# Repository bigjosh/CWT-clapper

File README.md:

# CWT-CLAPPER firmware, 2021 josh.com

## The mission

Be able to synchonise the clapping of the clappers, which requires sensing when the local clapper last clapped so that it can be positioned for the next clap. This is complicated becuase the only intentional sensor on board is a microphone and it is hard to differentiate beween the sound of a local clap and a nearby clap. 

## Theory of operation 

 1. As the cam rotates and pushes the blade, the spring is progessively streched. 
 2. The farther the spring is streched, the harder it is to strech it further (googgle "Hooke's law"). 
 3. The more force it takes to turn the motor, the more current it uses. 
 4. The more current the motor uses, the lower the voltage across the batteries becomes (google "internal resistance"). 
 5. We can indirectly measure the voltage across the battery with the internal ADC (https://wp.josh.com/2014/11/06/battery-fuel-guage-with-zero-parts-and-zero-pins-on-avr/)
 
 Q.E.D.: We can (sort of, barely, sextuple indirectly) measure the position of the blade by measuring the internal voltage 
 bandgap of the chip using the ADC!
  
 In practice, the change in ADC readings between the blade being fully open and fully shut is very small 
 and there is lots of noise also in these readings.
 
 So we aim to detect the most abupt change in that signal - the moment when the blade claps and the motor goes from pushing 
 a fully streched to spring to not pushing on the blade at all (there is a bit of a dead zone after a clap before the cam
 touches the blade again).
  
 To find this edge, we both filter out high freqnecy noise and amplify the longer running signal by taking periodic ADC samples 
 and summing these over a longer window. We have two consecutive windows, so when we get to the moment where one window is
 filled with samples from before the flap and the other is filled with samples from after the clap, there should be enough SNR to detect
 that by comparing the sums of all the values in each window. 
 
## Demo 
 
See them clap hare....
https://www.youtube.com/watch?v=MOf7x3NkilU&lc=UgzuyXRK9PwrqrHehkx4AaABAg.9SaJbr_eWT19Sc9pGRepJp

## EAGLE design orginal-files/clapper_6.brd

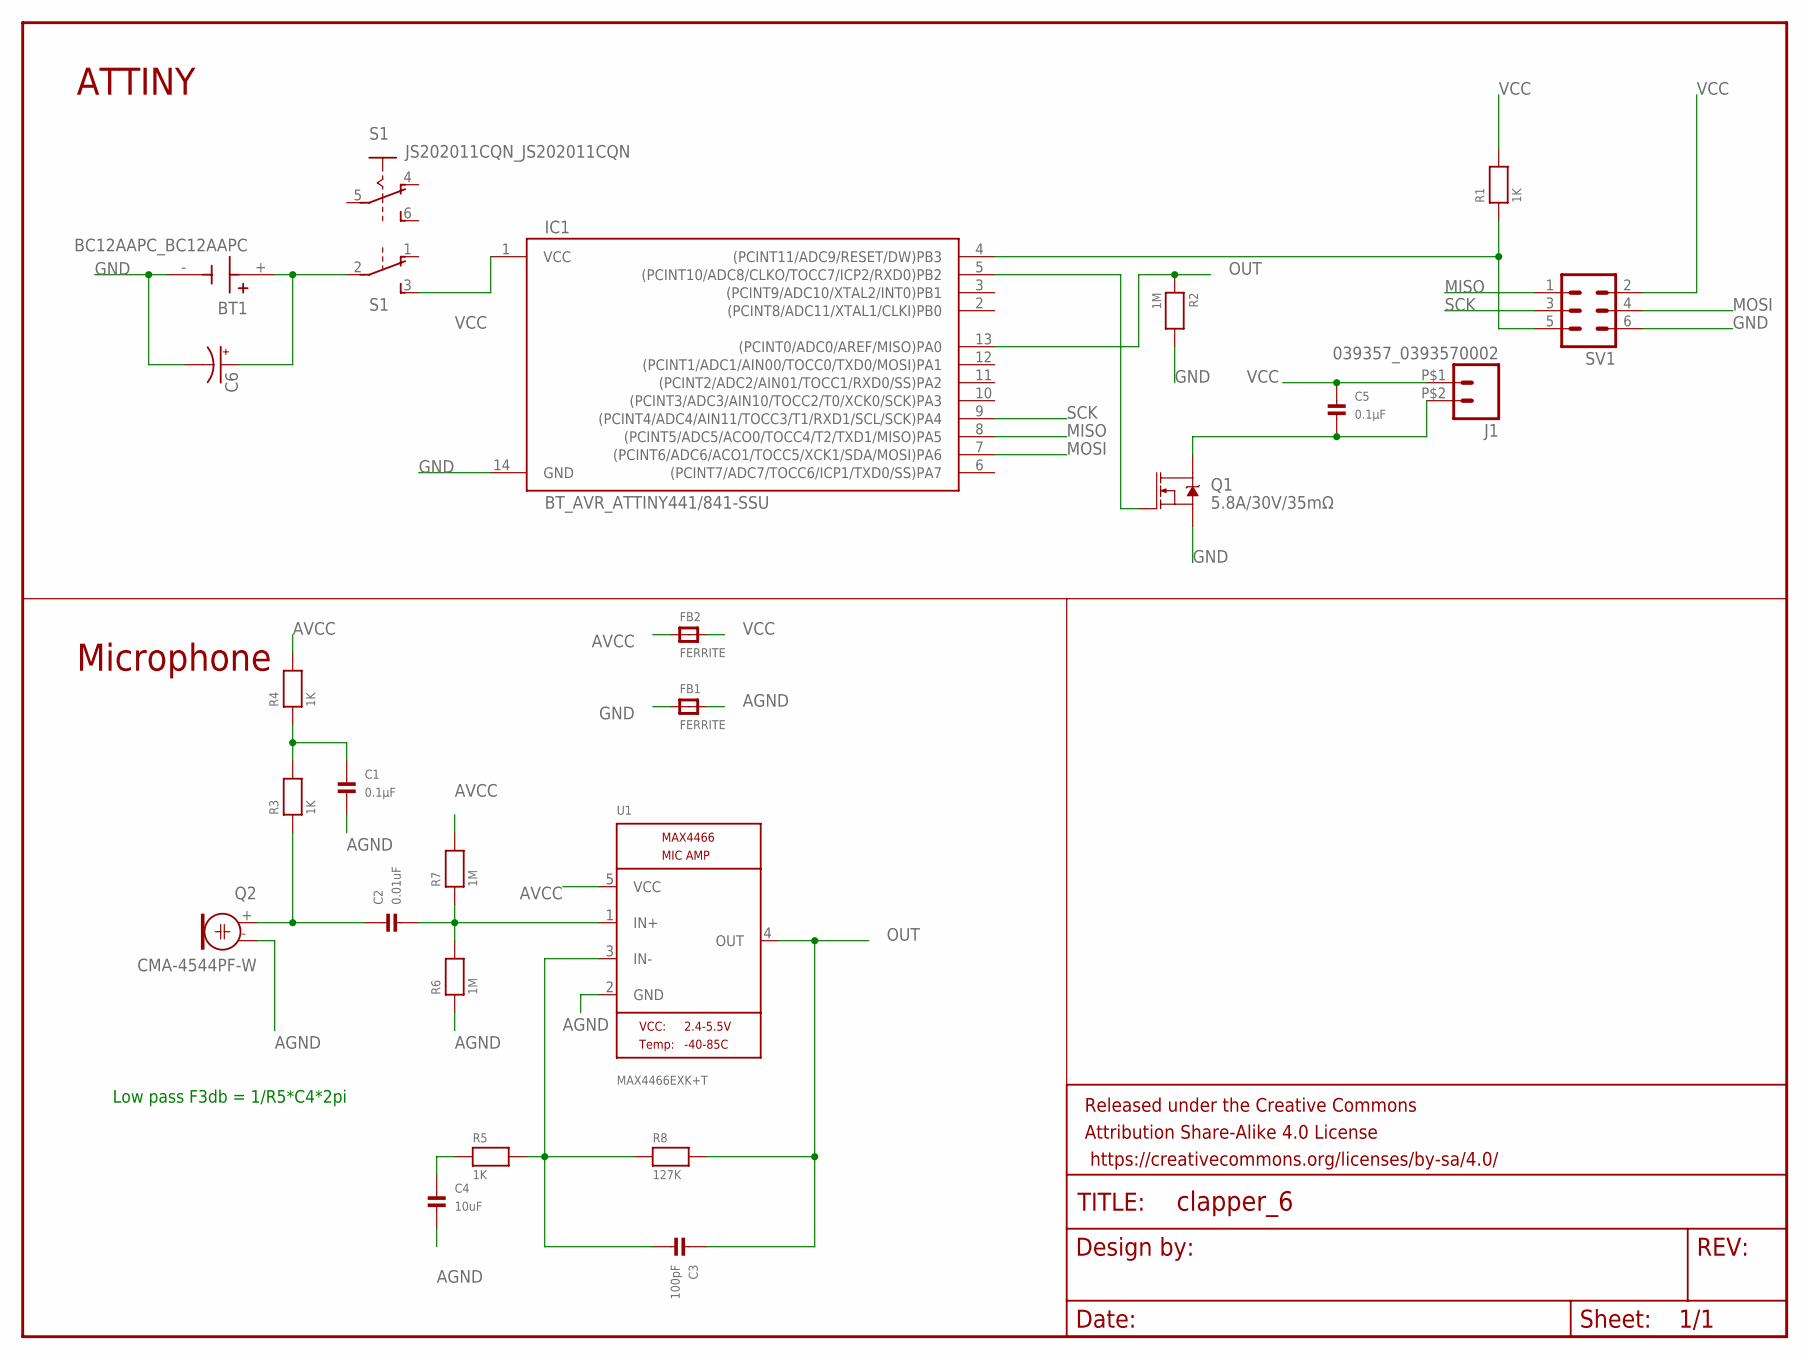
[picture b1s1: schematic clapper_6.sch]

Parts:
BT1: BC12AAPC_BC12AAPC; BC12AAPC_BAT_BC12AAPC
C1, C5: 0.1µF; MICROBUILDER_0805
C2: 0.01uF; MICROBUILDER_0805
C3: 100pF; MICROBUILDER_0805
C4: 10uF; MICROBUILDER_0805
C6: CPOL-USE2.5-6; E2,5-6
FB1, FB2: FERRITE; MICROBUILDER_0805
FRAME2: FRAME-LETTER; CREATIVE_COMMONS
IC1: BT_AVR_ATTINY441/841-SSU; BT_AVR_SOIC14N
J1: 039357_0393570002
Q1: 5.8A/30V/35mΩ; SOT23-3
Q2: CMA-4544PF-W; MICROBUILDER_ELECTRET_9.7
R1, R3, R4, R5: 1K; MICROBUILDER_0805
R2, R6, R7: 1M; MICROBUILDER_0805
R8: 127K; MICROBUILDER_0805
S1: JS202011CQN_JS202011CQN
SV1: CWT_MA03-2
U1: MAX4466EXK+T; MICROBUILDER_SC70-5

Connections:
AGND: C1.2, C4.2, FB1.2, Q2.- (1), R6.1, U1.2 (GND)
AVCC: FB2.1, R4.2, R7.2, U1.5 (VCC)
GND: BT1.-, C6.-, FB1.1, IC1.14 (GND), Q1.2 (S), R2.2, SV1.6
MISO: IC1.8 ((PCINT5/ADC5/ACO0/TOCC4/T2/TXD1/MISO)PA5), SV1.1
MOSI: IC1.7 ((PCINT6/ADC6/ACO1/TOCC5/XCK1/SDA/MOSI)P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), SV1.4
unnamed: C5.2, J1.P$2 (2), Q1.3 (D)
unnamed: BT1.+, C6.+, S1.2
unnamed: IC1.4 ((PCINT11/ADC9/RESET/DW)PB3), R1.1, SV1.5
unnamed: IC1.5 ((PCINT10/ADC8/CLKO/TOCC7/ICP2/RXD0)PB2), Q1.1 (G)
unnamed: C2.1, Q2.+ (2), R3.1
unnamed: C1.1, R3.2, R4.1
unnamed: C2.2, R6.2, R7.1, U1.1 (IN+)
unnamed: C3.2, R5.2, R8.1, U1.3 (IN-)
unnamed: C4.1, R5.1
OUT: C3.1, IC1.13 ((PCINT0/ADC0/AREF/MISO)PA0), R2.1, R8.2, U1.4 (OUT)
SCK: IC1.9 ((PCINT4/ADC4/AIN11/TOCC3/T1/RXD1/SCL/SC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), SV1.3
VCC: C5.1, FB2.2, IC1.1 (VCC), J1.P$1 (1), R1.2, S1.3 (S), SV1.2

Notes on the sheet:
Low pass F3db = 1/R5*C4*2pi
ATTINY
Microphone

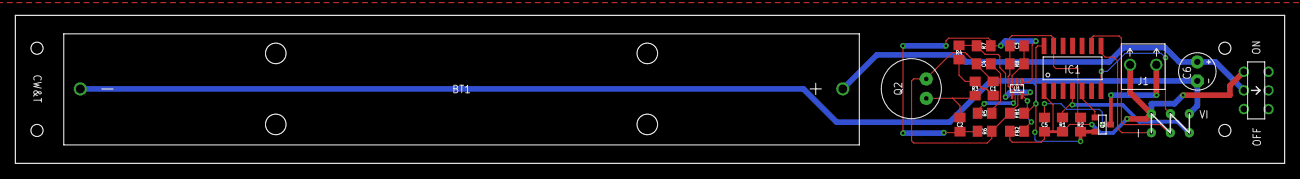
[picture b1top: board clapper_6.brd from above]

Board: 2 copper layers, 169.8 x 19.8 mm, 25 parts (0 on the bottom side), 17 nets.

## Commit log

2021-07-10 Three window moving average. Works only OK.
2021-07-10 Triple window filtered samples with hold-off. Seems to work!
2021-07-11 Ready to test detection on wider population!
    Should pause motor for 1 second after each clap.
2021-07-13 Add compiled versions for testing with CW&T machine
2021-07-13 Added attinycore change to empty bootloader file
2021-07-24 Pull out clap detection function, lower clap threshold
2021-07-24 Out of flash :/
2021-07-25 Too long, stopping right at the clap. Lets try simplifying...
2021-07-29 Add documentation files
2021-07-29 New double window-based detector seems to work 100% on all clappers!
2021-07-29 Everything works reliably, now just fold in the sound trigger
2021-07-29 Re-org files.
2021-08-29 Cleanup clapper10
2021-08-29 Mictester working
    Does not discriminate between claps and other loud noises, but works well.
2021-08-29 Rename motor functions to have `motor` in them
    Get ready for `mic` integration.
2021-08-29 It claps.
    Does motor calibration phase then goes into loop where it waits for sound and then claps and starts over.

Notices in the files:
parts and their libraries:
SparkFun-Aesthetics: Licensing: Creative Commons ShareAlike 4.0 International - https://creativecommons.org/licenses/by-sa/4.0
SparkFun-Aesthetics: Released under the Creative Commons Attribution Share-Alike 4.0 License
SparkFun-Aesthetics: https://creativecommons.org/licenses/by-sa/4.0
